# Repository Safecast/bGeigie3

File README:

## Readme

This is the Eagle CAD files for the bGeigie v2.0 (codename Delta) board.

This project is a part of the Safecast radiation monitoring project.
Find out more on [the Safecast website](http://www.safecast.org)

### License

2011 (c) Robin Scheibler
Creative Commons Attribution-ShareAlike 3.0 Unported (CC BY-SA 3.0)
For more details see (http://creativecommons.org/licenses/by-sa/3.0/)

## Design

### Main microcontroller

Atmega1284p.

### Power supply

The system is powered by a LiPo battery providing 4.2V at full charge and dies around 3.5V.

### Battery sensing

The Atmega1284p has two internal analog references: 1.1 or 2.56.

We need to sense the battery voltage between 4.2 and 3.5V.

Let's use a voltage divider with R1 = 300K and R2 = 100K.

Then Vs = R2/(R1+R2) = 1/4*Vin, giving a range of 1.05 to 0.875V roughly. We
decide to use the 1.1 reference. This gives use roughly 160 levels of
resolution.

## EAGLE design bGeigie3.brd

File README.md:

## bGeigie3

These are the Eagle CAD files for the bGeigie v3.0 (codename NX) board.

This project is a part of the Safecast radiation monitoring project.
Find out more on [the Safecast website](http://www.safecast.org)

_Note_: although the github repo is named `bGeigie2`, the content is really the **bGeigie3**.

## License

2011-2013 (c) Robin Scheibler
Creative Commons Attribution-ShareAlike 3.0 Unported (CC BY-SA 3.0)
For more details see (http://creativecommons.org/licenses/by-sa/3.0/)

## Produce a bGeigie3

### Gerber

The gerber files can be downloaded [here](https://dl.dropboxusercontent.com/u/78009186/files/bGeigie_v3.4_gerber.zip)

### BOM

The full BOM can be found [here](https://docs.google.com/spreadsheet/ccc?key=0AvXZ3hGhBSusdEQ3NjlfN2hRUnljeTNhNEF5WDNzVWc&usp=sharing).

### Software

* [Firmware](https://github.com/Safecast/SafecastBGeigie)
* [Modded arduino IDE](https://github.com/fakufaku/Arduino) [bin](https://github.com/downloads/fakufaku/Arduino/arduino-Safecast-20121019-macosx.zip)
* [Automated programming tools](https://github.com/Safecast/SCbG3-hexes)

## Tech notes

### Power supply

The system is powered by a LiPo battery providing 4.2V at full charge and dies around 3.5V.

### Battery sensing

The Atmega1284p has two internal analog references: 1.1 or 2.56.

We need to sense the battery voltage between 4.2 and 3.5V.

Let's use a voltage divider with R1 = 100K and R2 = 120K.

Then `Vs = R2/(R1+R2) = 0.54*Vin`, giving a range of 2.3V to 1.89V roughly. We
decide to use the 2.5 reference. This gives use roughly 170 levels of
resolution.

### 50 Ohm trace for the Radio and GPS antennas

* Wiki entry on [microstrips](http://en.wikipedia.org/wiki/Microstrip)
* Microstrip impedance [calculator](http://www.cepd.com/calculators/microstrip.htm)

As a starting point, I used the following values based on [PCB Fusion](http://www.seeedstudio.com/depot/fusion-pcb-service-p-835.html?cPath=185).

* Trace width: 2.815mm (need to look-up tolerance of printing service)
* Substrate height: 1.6mm (standard from PCB Fusion)
* Copper thickness: 0.035mm (guessed from PCB Fusion characteristics, inner layer ?)

give an impedance Z=50.04 Ohms.

### Possible printing services

* [PCB Fusion](http://www.seeedstudio.com/depot/fusion-pcb-service-p-835.html?cPath=185)
* [PCB Cart](http://www.pcbcart.com/) (seems to offer manufacturing too)
* [PCB Express](http://www.pcbexpress.com/)

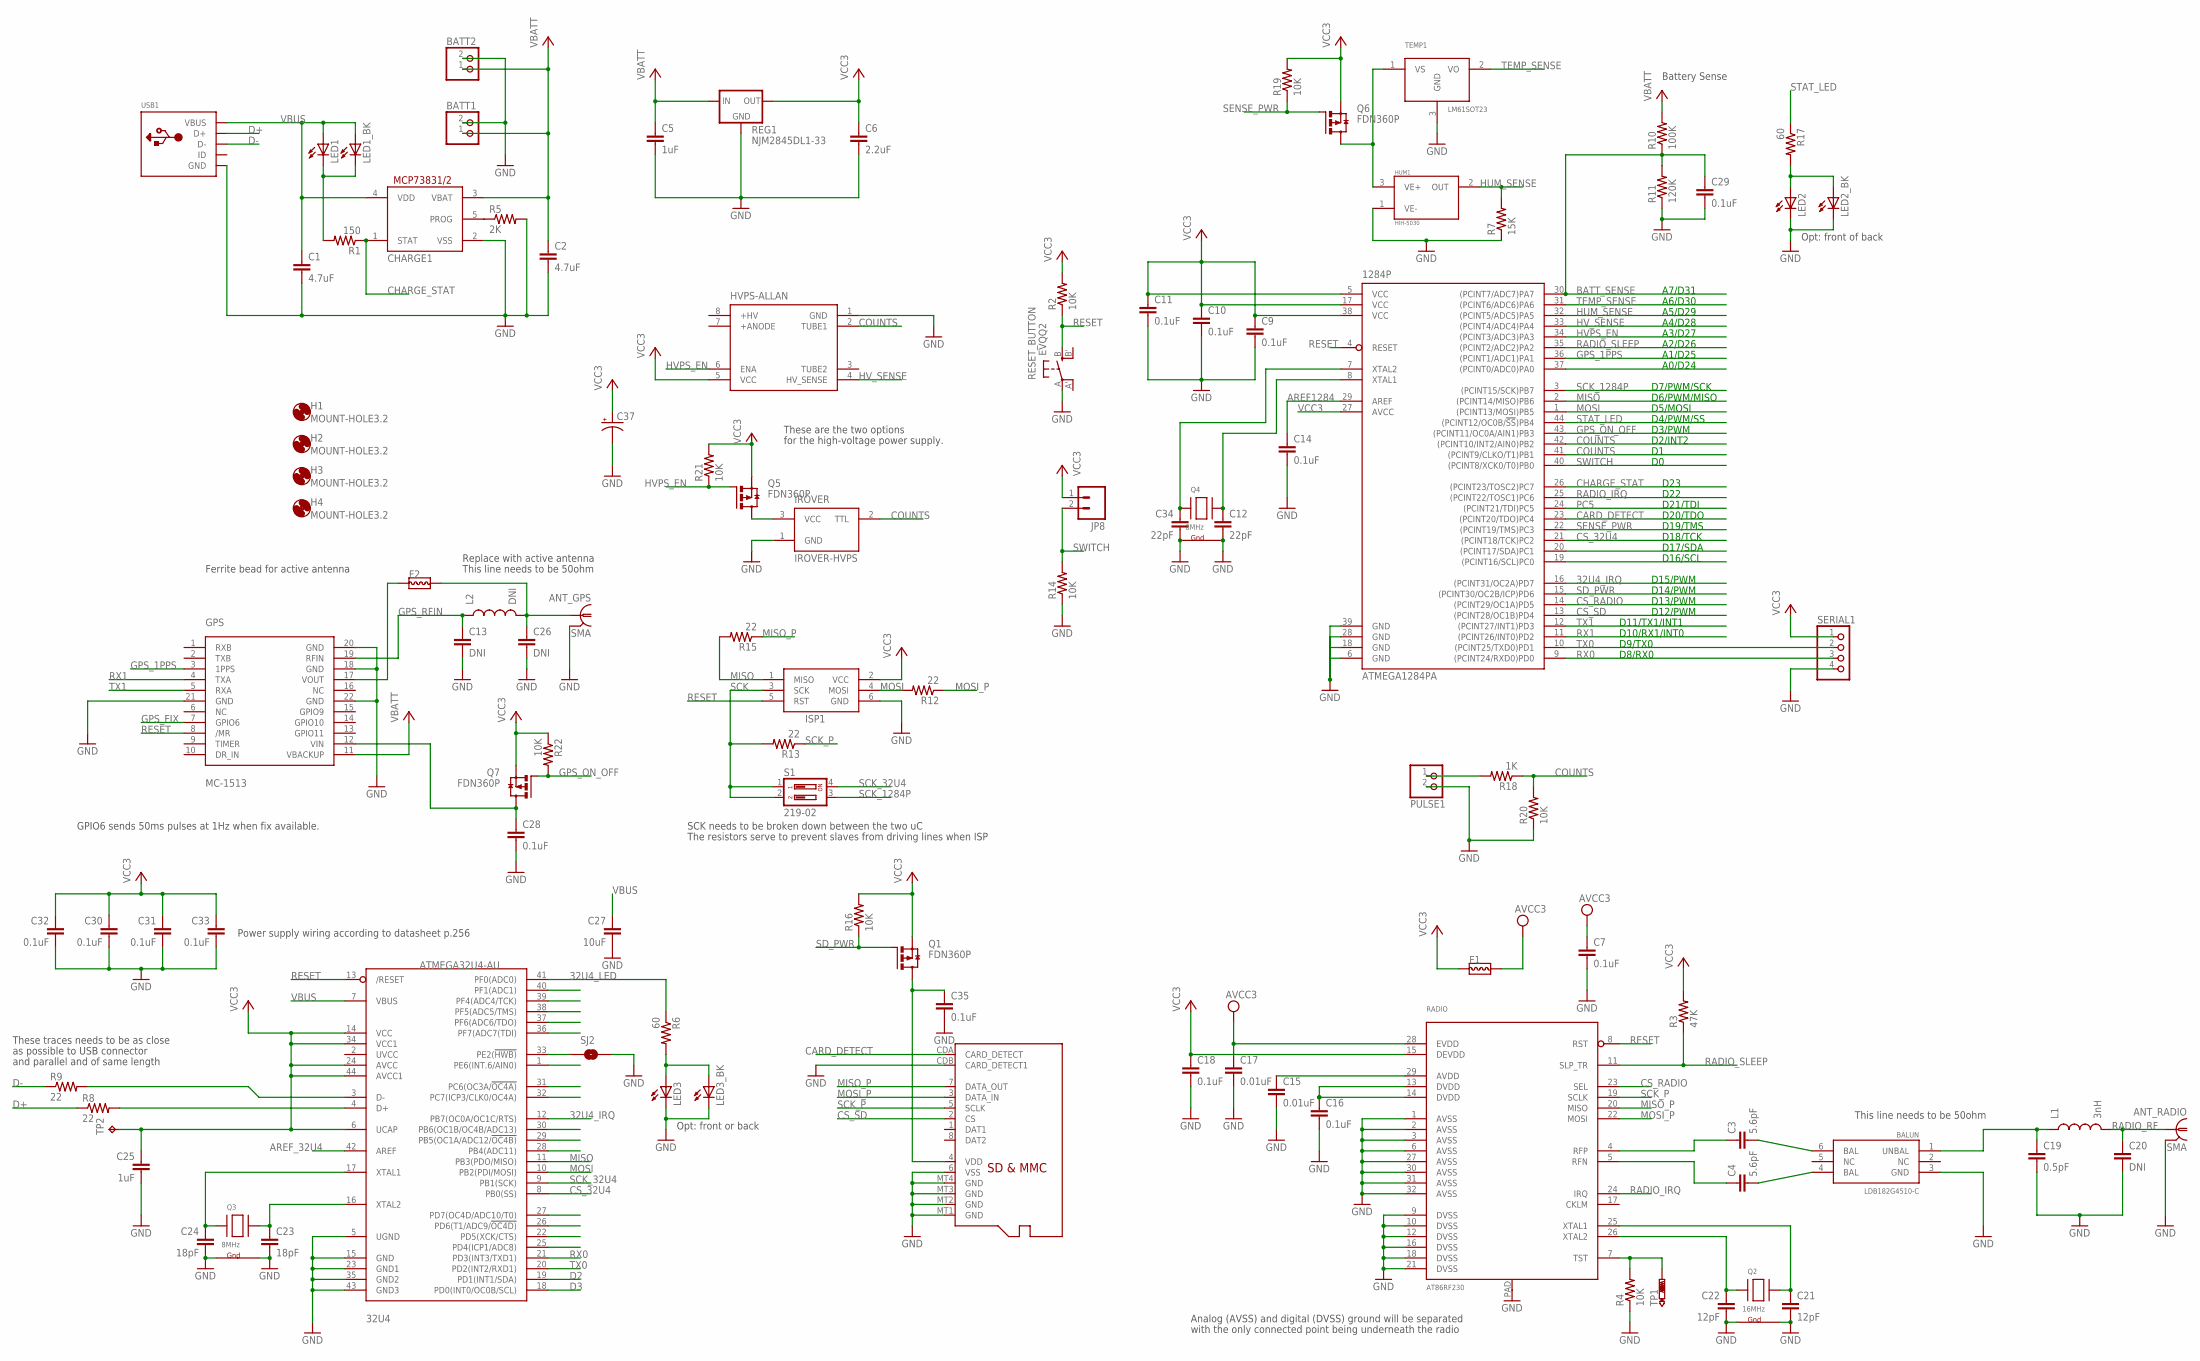
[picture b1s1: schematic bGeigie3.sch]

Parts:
32U4: ATMEGA32U4-AU; TQFP44
1284P: ATMEGA1284PA; TQFP44
ANT_GPS: SMA; LTI-SASF54GT
ANT_RADIO: SMA; LTI-SASF54GT
BALUN: LDB182G4510-C
BATT1, BATT2: JST_2PIN-THM; JST-PH-2-THM
C1, C2: 4.7uF; 0805
C3, C4: 5.6pF; 0402-CAP
C5: 1uF; 0805
C6: 2.2uF; 0805
C7, C9, C10, C11, C14, C16, C18, C28, C29, C30, C31, C32, C33, C35: 0.1uF; 0603-CAP
C12, C34: 22pF; 0603-CAP
C13, C20, C26: DNI; 0402-CAP
C15, C17: 0.01uF; 0603-CAP
C19: 0.5pF; 0402-CAP
C21, C22: 12pF; 0603-CAP
C23, C24: 18pF; 0603-CAP
C25: 1uF; 0603-CAP
C27: 10uF; 0805
C37: CPOL-USD/7343-31W; D/7343-31W
CHARGE1: MCP73831/OT; SOT23-5L
F1, F2: L-FERRITE-BEAD-0805; 0805
GPS: MC-1513; S4-1513
H1, H2, H3, H4: MOUNT-HOLE3.2; 3,2
HUM1: HIH-5030
HVPS-ALLAN: HVPS-ALLANV2-REVERSE; HVPS-ALLAN-V2-REVERSE
IROVER: IROVER-HVPS; IROVER
ISP1: AVRISP-6; AVRISP
JP8: M023.5MM; SCREWTERMINAL-3.5MM-2
L1: 3nH; C0402
L2: DNI; C0402
LED1, LED1_BK, LED2, LED2_BK, LED3, LED3_BK: LEDCHIPLED_0603; CHIPLED_0603
PULSE1: JST_2PIN-THM; JST-PH-2-THM
Q1, Q5, Q6, Q7: FDN360P; SUPER-SOT3
Q2: 16MHz; NX3225
Q3, Q4: 8MHz; CRYSTAL-5032
R1: 150; R0805
R2, R4, R14, R16, R19, R20, R21, R22: 10K; R0603
R3: 47K; R0603
R5: 2K; R0603
R6, R17: 60; R0805
R7: 15K; R0603
R8, R9, R12, R13, R15: 22; R0603
R10: 100K; R0603
R11: 120K; R0603
R18: 1K; R0603
RADIO: AT86RF230; 32QN1
REG1: NJM2845DL1-33; DPACK
RESET_BUTTON: EVQQ2; EVQ-Q2
S1: 219-02; CTS-219-02
SD: MICROSD; DM3AT-SF-PEJM5
SERIAL1: PINHD-1X4; 1X04
SJ2: SOLDERJUMPERTRACE; SJ_2S-TRACE
TEMP1: LM61SOT23; SOT23
TP1: PTR1B1,27; B1,27
TP2: TPTP15SQ; TP15SQ
USB1: USBMINIB; USB-MINIB

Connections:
32U4_IRQ: 32U4.12 (PB7(OC0A/OC1C/RTS)), 1284P.16 ((PCINT31/OC2A)PD7)
32U4_LED: 32U4.41 (PF0(ADC0)), R6.1
32U4_PC7: 32U4.32 (PC7(ICP3/CLK0/OC4A))
AREF1284: 1284P.29 (AREF), C14.1
AREF_32U4: 32U4.42 (AREF)
AVCC3: C7.1, C17.1, F1.2, RADIO.28 (EVDD)
BATT_SENSE: 1284P.30 ((PCINT7/ADC7)PA7), C29.1, R10.1, R11.2
CARD_DETECT: 1284P.23 ((PCINT20/TDO)PC4), SD.CDA (CARD_DETECT)
CHARGE_STAT: 1284P.26 ((PCINT23/TOSC2)PC7), CHARGE1.1 (STAT), R1.1
COUNTS: 1284P.41 ((PCINT9/CLKO/T1)PB1), 1284P.42 ((PCINT10/INT2/AIN0)PB2), HVPS-ALLAN.2 (TUBE1), IROVER.2 (TTL), R18.1, R20.2
CS_32U4: 32U4.8 (PB0(SS)), 1284P.21 ((PCINT18/TCK)PC2)
CS_RADIO: 1284P.14 ((PCINT29/OC1A)PD5), RADIO.23 (SEL)
CS_SD: 1284P.13 ((PCINT28/OC1B)PD4), SD.2 (CS)
D2: 32U4.19 (PD1(INT1/SDA))
D3: 32U4.18 (PD0(INT0/OC0B/SCL))
D+: R8.1, USB1.D+
D-: R9.1, USB1.D-
GND: 32U4.5 (UGND), 32U4.15 (GND), 32U4.23 (GND1), 32U4.35 (GND2), 32U4.43 (GND3), 1284P.6 (GND), 1284P.18 (GND), 1284P.28 (GND), 1284P.39 (GND), ANT_GPS.2 (GND), ANT_GPS.3 (GND), ANT_GPS.4 (GND), ANT_GPS.5 (GND), ANT_RADIO.2 (GND), ANT_RADIO.3 (GND), ANT_RADIO.4 (GND), ANT_RADIO.5 (GND), BALUN.3 (GND), BATT1.2 (1), BATT2.2 (1), C1.2, C2.2, C5.2, C6.2, C7.2, C9.2, C10.2, C11.2, C12.2, C13.2, C14.2, C15.2, C16.2, C17.2, C18.2, C19.2, C20.2, C21.2, C22.2, C23.2, C24.2, C25.2, C26.2, C27.2, C28.2, C29.2, C30.2, C31.2, C32.2, C33.2, C34.2, C35.2, C37.-, CHARGE1.2 (VSS), GPS.18 (GND), GPS.20 (GND), GPS.21 (GND), GPS.22 (GND), HUM1.1 (VE-), HVPS-ALLAN.1 (GND), IROVER.1 (GND), ISP1.6 (GND), LED2.C, LED2_BK.C, LED3.C, LED3_BK.C, PULSE1.2 (1), Q2.2 (G2), Q2.4 (G1), Q3.2 (G1), Q3.4 (G2), Q4.2 (G1), Q4.4 (G2), R4.1, R5.2, R7.1, R11.1, R14.1, R20.1, RADIO.1 (AVSS), RADIO.2 (AVSS), RADIO.3 (AVSS), RADIO.6 (AVSS), RADIO.9 (DVSS), RADIO.10 (DVSS), RADIO.12 (DVSS), RADIO.16 (DVSS), RADIO.18 (DVSS), RADIO.21 (DVSS), RADIO.27 (AVSS), RADIO.30 (AVSS), RADIO.31 (AVSS), RADIO.32 (AVSS), RADIO.PAD, REG1.4 (GND), RESET_BUTTON.A, SD.6 (VSS), SD.CDB (CARD_DETECT1), SD.MT1 (GND), SD.MT2 (GND), SD.MT3 (GND), SD.MT4 (GND), SERIAL1.4, SJ2.2, TEMP1.3 (GND), USB1.GND
GPS_1PPS: 1284P.36 ((PCINT1/ADC1)PA1), GPS.3 (1PPS)
GPS_FIX: GPS.7 (GPIO6)
GPS_ON_OFF: 1284P.43 ((PCINT11/OC0A/AIN1)PB3), Q7.1 (G), R22.2
GPS_RFIN: C13.1, GPS.19 (RFIN), L2.1
HUM_SENSE: 1284P.32 ((PCINT5/ADC5)PA5), HUM1.2 (OUT), R7.2
HVPS_EN: 1284P.34 ((PCINT3/ADC3)PA3), HVPS-ALLAN.6 (ENA), Q5.1 (G), R21.1
HV_SENSE: 1284P.33 ((PCINT4/ADC4)PA4), HVPS-ALLAN.4 (HV_SENSE)
MISO: 32U4.11 (PB3(PDO/MISO)), 1284P.2 ((PCINT14/MISO)PB6), ISP1.1 (MISO), R15.2
MISO_P: R15.1, RADIO.20 (MISO), SD.7 (DATA_OUT)
MOSI: 32U4.10 (PB2(PDI/MOSI)), 1284P.1 ((PCINT13/MOSI)PB5), ISP1.4 (MOSI), R12.2
MOSI_P: R12.1, RADIO.22 (MOSI), SD.3 (DATA_IN)
unnamed: 32U4.16 (XTAL2), C23.1, Q3.3 (X2)
unnamed: LED1.C, LED1_BK.C, R1.2
unnamed: PULSE1.1 (2), R18.2
unnamed: CHARGE1.5 (PROG), R5.1
unnamed: BALUN.4 (BAL), C4.2
unnamed: 1284P.8 (XTAL1), C12.1, Q4.3 (X2)
unnamed: 1284P.7 (XTAL2), C34.1, Q4.1 (X1)
unnamed: C16.1, RADIO.13 (DVDD), RADIO.14 (DVDD)
unnamed: C15.1, RADIO.29 (AVDD)
unnamed: ANT_GPS.1, C26.1, F2.2, L2.2
unnamed: C21.1, Q2.3 (X2), RADIO.25 (XTAL1)
unnamed: C22.1, Q2.1 (X1), RADIO.26 (XTAL2)
unnamed: F2.1, GPS.17 (VOUT)
unnamed: IROVER.3 (VCC), Q5.3 (D)
unnamed: LED3.A, LED3_BK.A, R6.2
unnamed: R4.2, RADIO.7 (TST), TP1.TP
unnamed: BALUN.6 (BAL), C3.2
unnamed: C4.1, RADIO.5 (RFN)
unnamed: C3.1, RADIO.4 (RFP)
unnamed: BALUN.1 (UNBAL), C19.1, L1.1
unnamed: C28.1, GPS.12 (VIN), Q7.3 (D)
unnamed: 32U4.17 (XTAL1), C24.1, Q3.1 (X1)
unnamed: LED2.A, LED2_BK.A, R17.2
unnamed: 32U4.3 (D-), R9.2
unnamed: 32U4.4 (D+), R8.2
unnamed: 32U4.33 (PE2(!HWB)), SJ2.1
PA0: 1284P.37 ((PCINT0/ADC0)PA0)
PC0: 1284P.19 ((PCINT16/SCL)PC0)
PC1: 1284P.20 ((PCINT17/SDA)PC1)
PC5: 1284P.24 ((PCINT21/TDI)PC5)
RADIO_IRQ: 1284P.25 ((PCINT22/TOSC1)PC6), RADIO.24 (IRQ)
RADIO_RF: ANT_RADIO.1, C20.1, L1.2
RADIO_SLEEP: 1284P.35 ((PCINT2/ADC2)PA2), R3.1, RADIO.11 (SLP_TR)
RESET: 32U4.13 (/RESET), 1284P.4 (RESET), GPS.8 (/MR), ISP1.5 (RST), R2.1, RADIO.8 (RST), RESET_BUTTON.B (S)
RX0: 32U4.21 (PD3(INT3/TXD1)), 1284P.9 ((PCINT24/RXD0)PD0), SERIAL1.3
RX1: 1284P.11 ((PCINT26/INT0)PD2), GPS.4 (TXA)
SCK: ISP1.3 (SCK), R13.2, S1.1, S1.2
SCK_32U4: 32U4.9 (PB1(SCK)), S1.4
SCK_1284P: 1284P.3 ((PCINT15/SCK)PB7), S1.3
SCK_P: R13.1, RADIO.19 (SCLK), SD.5 (SCLK)
SD_PWR: 1284P.15 ((PCINT30/OC2B/ICP)PD6), Q1.1 (G), R16.1
SENSE: HUM1.3 (VE+), Q6.3 (D), TEMP1.1 (VS)
SENSE_PWR: 1284P.22 ((PCINT19/TMS)PC3), Q6.1 (G), R19.1
STAT_LED: 1284P.44 ((PCINT12/OC0B/!SS!)PB4), R17.1
SWITCH: 1284P.40 ((PCINT8/XCK0/T0)PB0), JP8.2, R14.2
TEMP_SENSE: 1284P.31 ((PCINT6/ADC6)PA6), TEMP1.2 (VO)
TX0: 32U4.20 (PD2(INT2/RXD1)), 1284P.10 ((PCINT25/TXD0)PD1), SERIAL1.2
TX1: 1284P.12 ((PCINT27/INT1)PD3), GPS.5 (RXA)
VBATT: BATT1.1 (2), BATT2.1 (2), C2.1, C5.1, CHARGE1.3 (VBAT), GPS.11 (VBACKUP), R10.2, REG1.1 (IN)
VBUS: 32U4.7 (VBUS), C1.1, C27.1, CHARGE1.4 (VDD), LED1.A, LED1_BK.A, USB1.VBUS
VCC3: 32U4.6 (UCAP), 32U4.14 (VCC), 32U4.24 (AVCC), 32U4.34 (VCC1), 32U4.44 (AVCC1), 1284P.5 (VCC), 1284P.17 (VCC), 1284P.27 (AVCC), 1284P.38 (VCC), C6.1, C9.1, C10.1, C11.1, C18.1, C25.1, C30.1, C31.1, C32.1, C33.1, C37.+, F1.1, HVPS-ALLAN.5 (VCC), ISP1.2 (VCC), JP8.1, Q1.2 (S), Q5.2 (S), Q6.2 (S), Q7.2 (S), R2.2, R3.2, R16.2, R19.2, R21.2, R22.1, RADIO.15 (DEVDD), REG1.3 (OUT), SERIAL1.1, TP2.TP
VDD: C35.1, Q1.3 (D), SD.4 (VDD)

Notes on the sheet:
D2/INT2
D3/PWM
D4/PWM/SS
D5/MOSI
D6/PWM/MISO
D7/PWM/SCK
D8/RX0
D9/TX0
D11/TX1/INT1
D10/RX1/INT0
D12/PWM
D13/PWM
D14/PWM
D15/PWM
D16/SCL
D17/SDA
D18/TCK
D19/TMS
D20/TDO
D21/TDI
D22
D23
A0/D24
A1/D25
A2/D26
A3/D27
A4/D28
A5/D29
A6/D30
A7/D31
Battery Sense
GPIO6 sends 50ms pulses at 1Hz when fix available.
SCK needs to be broken down between the two uC
The resistors serve to prevent slaves from driving lines when ISP
This line needs to be 50ohm
These traces needs to be as close
as possible to USB connector
and parallel and of same length
Replace with active antenna
Analog (AVSS) and digital (DVSS) ground will be separated

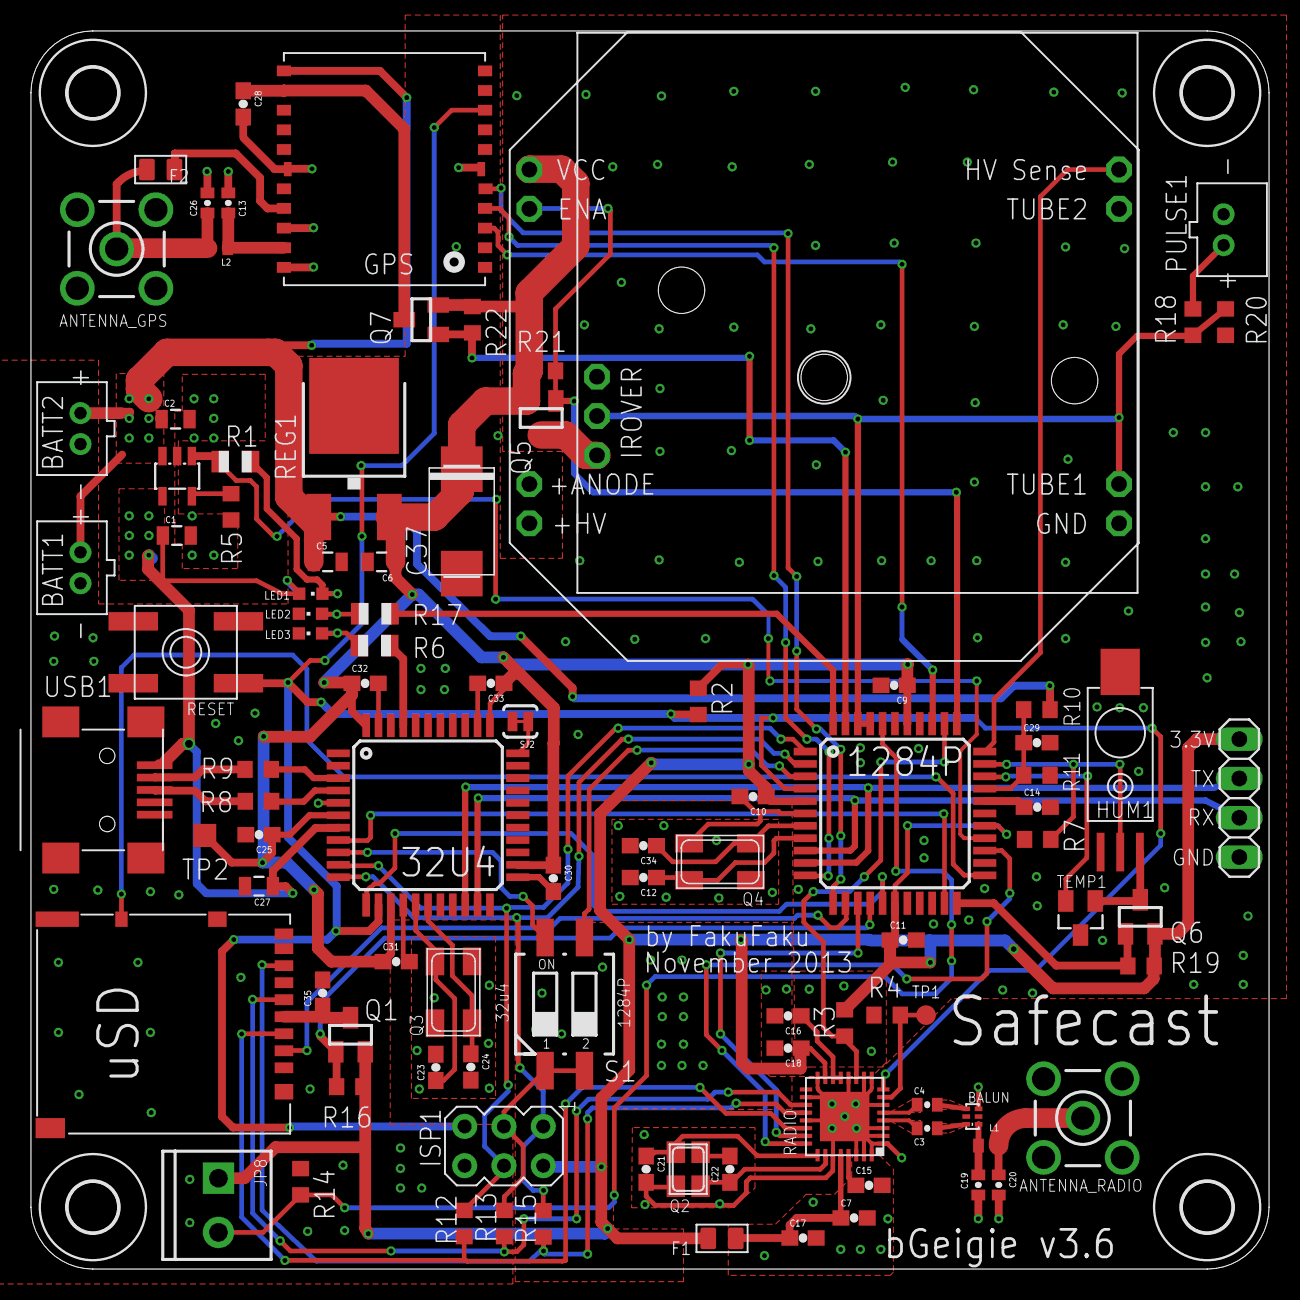
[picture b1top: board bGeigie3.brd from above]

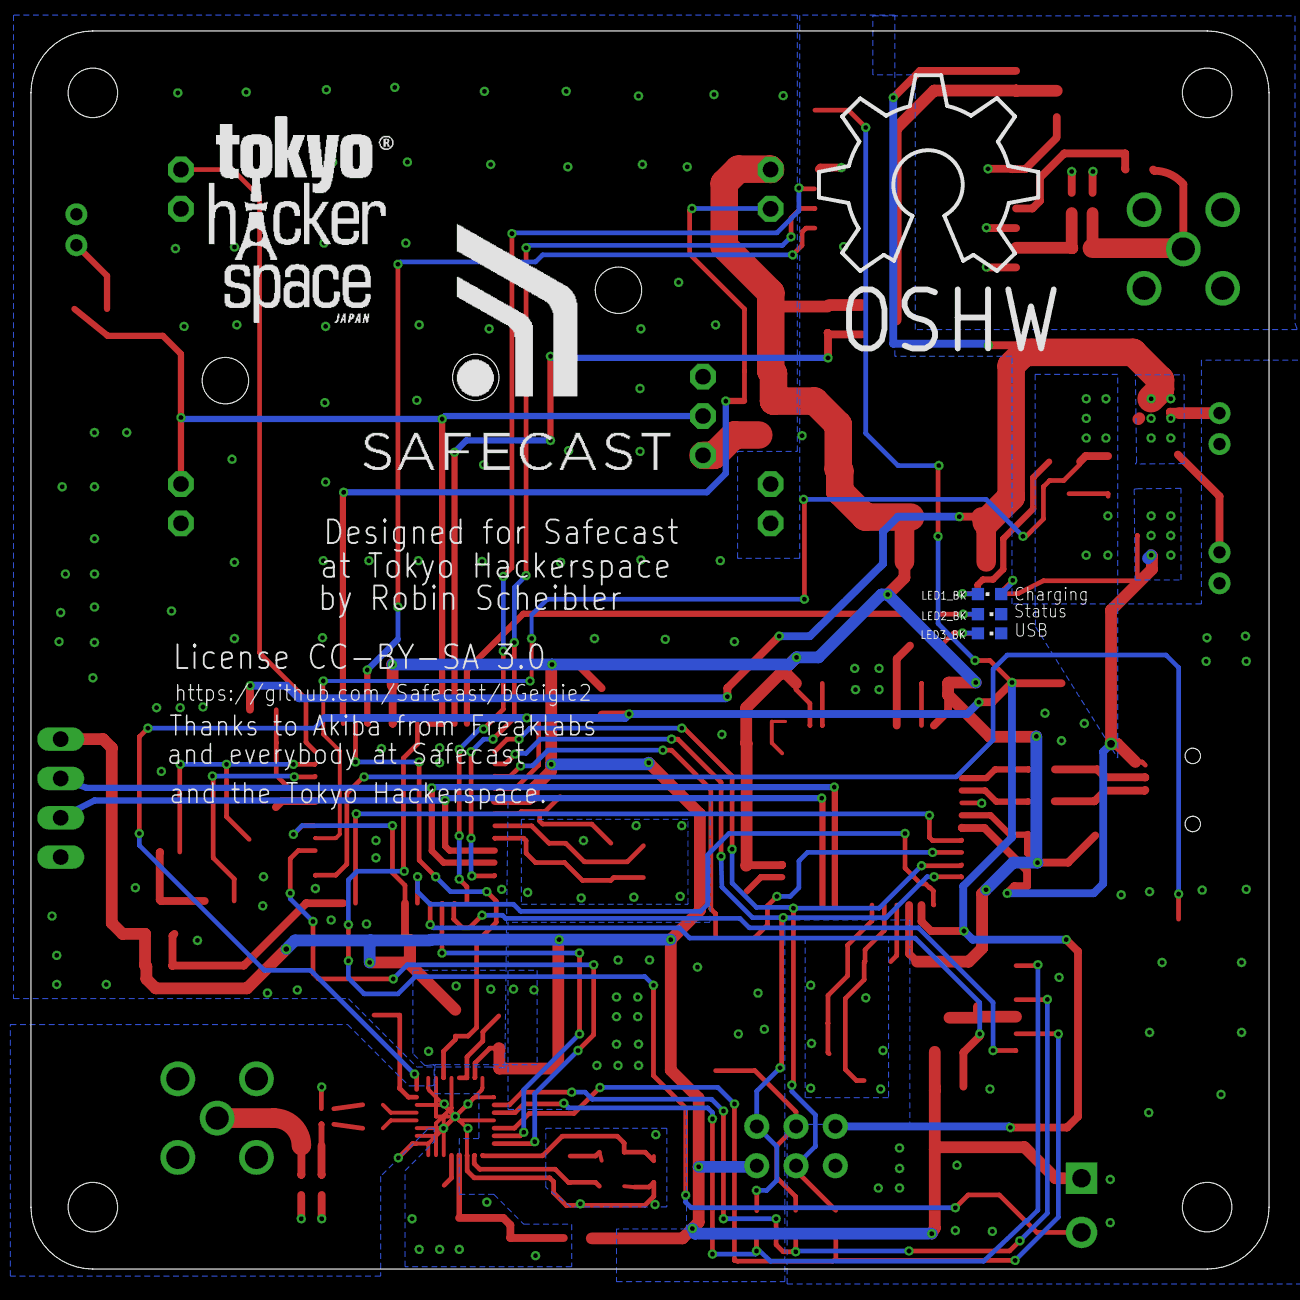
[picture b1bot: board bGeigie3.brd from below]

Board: 2 copper layers, 80.0 x 80.0 mm, 107 parts (6 on the bottom side), 72 nets.

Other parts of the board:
U$1: SAFECAST_LOGO
U$3: THS
U$4: OSHW_10X500_NOTEXT

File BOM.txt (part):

Partlist

Exported from bGeigie2.sch at 13.09.12 17:58

EAGLE Version 5.11.0 Copyright (c) 1988-2010 CadSoft

Part         Value                Device               Package               Library          Sheet

32U4         ATMEGA32U4-AU        ATMEGA32U4-AU        TQFP44                adafruit         1
1284P        ATMEGA1284PA         ATMEGA1284PA         TQFP44                Robin            1
ANT_GPS      SMA                  LTI-SASF54GT         LTI-SASF54GT          con-coax         1
ANT_RADIO    SMA                  LTI-SASF54GT         LTI-SASF54GT          con-coax         1
BALUN        LDB182G4510-C        LDB182G4510-C        LDB182G4510-C         Robin            1
BATT1                             JST_2PIN-THM         JST-PH-2-THM          adafruit         1
BATT2                             JST_2PIN-THM         JST-PH-2-THM          adafruit         1
C1           4.7uF                CAP0805              0805                  SparkFun         1
C2           4.7uF                CAP0805              0805                  SparkFun         1
C3           5.6pF                CAP0402-CAP          0402-CAP              SparkFun         1
C4           5.6pF                CAP0402-CAP          0402-CAP              SparkFun         1
C5           1uF                  CAP0805              0805                  SparkFun         1
C6           2.2uF                CAP0805              0805                  SparkFun         1
C7           0.1uF                CAP0603-CAP          0603-CAP              SparkFun         1
C8           0.1uF                CAP0603-CAP          0603-CAP              SparkFun         1
C9           0.1uF                CAP0603-CAP          0603-CAP              SparkFun         1
C10          0.1uF                CAP0603-CAP          0603-CAP              SparkFun         1
C11          0.1uF                CAP0603-CAP          0603-CAP              SparkFun         1
C12          22pF                 CAP0603-CAP          0603-CAP              SparkFun         1
C13          DNI                  CAP0402-CAP          0402-CAP              SparkFun         1
C14          0.1uF                CAP0603-CAP          0603-CAP              SparkFun         1
C15          0.01uF               CAP0603-CAP          0603-CAP              SparkFun         1
C16          0.1uF                CAP0603-CAP          0603-CAP              SparkFun         1
C17          0.01uF               CAP0603-CAP          0603-CAP              SparkFun         1
C18          0.1uF                CAP0603-CAP          0603-CAP              SparkFun         1
C19          0.5pF                CAP0402-CAP          0402-CAP              SparkFun         1
C20          DNI                  CAP0402-CAP          0402-CAP              SparkFun         1
C21          12pF                 CAP0603-CAP          0603-CAP              SparkFun         1
C22          12pF                 CAP0603-CAP          0603-CAP              SparkFun         1
C23          18pF                 CAP0603-CAP          0603-CAP              SparkFun         1
C24          18pF                 CAP0603-CAP          0603-CAP              SparkFun         1
C25          1uF                  CAP0603-CAP          0603-CAP              SparkFun         1
C26          DNI                  CAP0402-CAP          0402-CAP              SparkFun         1
C27          10uF                 CAP0805              0805                  SparkFun         1
C28          0.1uF                CAP0603-CAP          0603-CAP              SparkFun         1
C29          0.1uF                CAP0603-CAP          0603-CAP              SparkFun         1
C30          0.1uF                CAP0603-CAP          0603-CAP              SparkFun         1
C31          0.1uF                CAP0603-CAP          0603-CAP              SparkFun         1
C32          0.1uF                CAP0603-CAP          0603-CAP              SparkFun         1
C33          0.1uF                CAP0603-CAP          0603-CAP              SparkFun         1
C34          22pF                 CAP0603-CAP          0603-CAP              SparkFun         1
C35          0.1uF                CAP0603-CAP          0603-CAP              SparkFun         1
C36          0.1uF                CAP0603-CAP          0603-CAP              SparkFun         1
C37                               CPOL-USD/7343-31W    D/7343-31W            Robin            1
CHARGE1      MCP73831/OT          MCP73831/OT          SOT23-5L              adafruit         1
F1                                L-FERRITE-BEAD-0805  0805                  Discreter        1
F2                                L-FERRITE-BEAD-0805  0805                  Discreter        1
GPS          MC-1513              MC-1513              S4-1513               Robin            1
HUM1         HIH-5030             HIH-5030             HIH-5030              Robin            1
HVPS-ALLAN   HVPS-ALLANV2-REVERSE HVPS-ALLANV2-REVERSE HVPS-ALLAN-V2-REVERSE Robin            1
IROVER       IROVER-HVPS          IROVER-HVPS          IROVER                Robin            1
ISP1         AVRISP-6             AVRISP-6             AVRISP                adafruit         1
JP2                               PINHD-1X6/90         1X06/90               pinhead          1
JP3                               PINHD-1X6/90         1X06/90               pinhead          1
JP8                               M023.5MM             SCREWTERMINAL-3.5MM-2 SparkFun         1
L1           3nH                  INDUCTOR0402         C0402                 SparkFun         1
L2           DNI                  INDUCTOR0402         C0402                 SparkFun         1
LED1                              LEDCHIPLED_0603      CHIPLED_0603          adafruit         1
LED1_BK                           LEDCHIPLED_0603      CHIPLED_0603          adafruit         1
LED2                              LEDCHIPLED_0603      CHIPLED_0603          adafruit         1
LED2_BK                           LEDCHIPLED_0603      CHIPLED_0603          adafruit         1
LED3                              LEDCHIPLED_0603      CHIPLED_0603          adafruit         1
LED3_BK                           LEDCHIPLED_0603      CHIPLED_0603          adafruit         1
PULSE1                            JST_2PIN-THM         JST-PH-2-THM          adafruit         1
Q1           FDN360P              FDN360P              SUPER-SOT3            transistor-power 1
Q2           16MHz                XTAL-4-3225          NX3225                adafruit         1
Q3           8MHz                 XTAL-4               CRYSTAL-5032          Robin            1
Q4           8MHz                 XTAL-4               CRYSTAL-5032          Robin            1
Q5           FDN360P              FDN360P              SUPER-SOT3            transistor-power 1
Q6           FDN360P              FDN360P              SUPER-SOT3            transistor-power 1
Q7           FDN360P              FDN360P              SUPER-SOT3            transistor-power 1
R1           150                  R-US_R0805           R0805                 adafruit         1
R2           10K                  R-US_R0603           R0603                 adafruit         1
R3           47K                  R-US_R0603           R0603                 adafruit         1
R4           10K                  R-US_R0603           R0603                 adafruit         1
R5           2K                   R-US_R0603           R0603                 adafruit         1
R6           60                   R-US_R0805           R0805                 adafruit         1
R7           15K                  R-US_R0603           R0603                 adafruit         1
R8           22                   R-US_R0603           R0603                 adafruit         1
R9           22                   R-US_R0603           R0603                 adafruit         1
R10          100K                 R-US_R0603           R0603                 adafruit         1
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
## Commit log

2011-12-08 Added content and License to README file. Added .gitignore file and placeholder file for Bill Of Material (BOM.txt).
2011-12-08 Added junk files from Eagle CAD to .gitignore
2011-12-08 Added TODO.txt file to keep track of what's left to do.
2011-12-08 Added png schematics file
2011-12-19 Commiting current status of 'low-power' version.
2011-12-27 Added chipselects, IRQ. 1284p is now master of all devices. Optional serial connection between 32u4 and 1284p.
2012-01-06 Added boost converter. Edited TODO with current tasks. Now board is at 3.3V.
2012-01-07 Started to check all foot print, began the BOM.
2012-01-09 UPdated todo, started checking all footprints.
2012-01-12 More details. Updated TODO.
2012-01-12 Suffixed README with markdown extension.
2012-01-12 Suffixed README with .md.
2012-01-12 Updated PNG
2012-01-13 Added 'breakout 32u4 pins' to todo list.
2012-01-13 Updated README with impedance of RF line (GPS, Radio), and printing services.
2012-01-13 More changes
2012-01-13 Added board file.|
2012-01-17 Schematics nearly done. (Will need HVPS soon though). Added and started the board layout.
2012-01-17 Added layout png
2012-01-17 Updated schematics png, .gitignore.
2012-01-19 Advanced board layout a bit. Corrected few bugs in schematics.
2012-02-19 Moved GPS, laid radio, more wires laid out.
2012-02-20 Pulled some more wires. Finished GPS.
2012-02-20 Updated BOM, layout and schematics png.
2012-02-25 Mostly finished routing.
2012-02-25 Modified High Voltage board for v2.0. Updated PNGs.
2012-02-27 Corrected crystal. Cleaned labels. Added pull-down on audio jack. Added humidity sensor. Transistor on sensors supplies.
2012-02-29 Added iRover trace. Connected 32u4 to interrupt of 1284p. Updated BOM.
2012-03-01 Corrected hole sizes of iRover and Allan's HVPS board.
2012-03-05 Corrected audio jack footprint.
2012-03-05 Added Safecast and THS logo.
2012-03-06 Removed bottom LED labels.
2012-03-06 Added SMD footprint for LEDs on backside.
2012-03-07 Corrected values of R10, R11 and C5.
2012-03-07 Changed info about battery sensing in README.
2012-03-08 Changed footprint of 8MHz crystals.
2012-03-31 Rerouted MOSI to 32u4
2012-04-11 Replaced bipolar pnp transistors by p-channel mosfet.
2012-04-11 Added mosfet on GPS powerline. Modified GPS library part to conform to datasheet v1.4.
2012-04-12 Placed and routed MOSFET transistors.
2012-04-12 Added LED for 32u4 on pin 13.
2012-04-12 Moved 1284p led to arduino digital pin 13, routed 32u4 led on board.
2012-04-12 Corrected SPI bug.
2012-04-12 Updated PNGs.
2012-04-12 Make board corners rounded.
2012-04-24 Added credits, logo and art. Moved bead from gps antenna power.
2012-06-08 Reduced board size. Implemented everything learnt from prototypes. Go to version 3.3.
2012-06-08 Small connection was missing on a radio pad.
2012-06-09 Put C13, C26, and C19, C20 to different grounds. Updated layout PNG.
2012-06-09 Finalizing before fab.
2012-06-22 Corrected bug (unconnected wires). Rewired VCC so that power to 32u4 and 1284 are fairly independant, easy to split.
2012-07-07 Added big tantalum cap on power supply line to HVPS.
2012-07-27 Added dot in silkscreen of GPS footprint for orientation of chip.
2012-07-27 Renamed board png to bGeigie2_brd.png for consistency.
2012-09-13 Added top and bottom PNGs. Added mechanical design files for lazer cutting.
2012-09-13 Moved some labels. Added some silkscreen for 8MHz crystals. Added some tDocu for art on humidity sensor.
2012-10-28 Updated silkscreen with missing labels.
2013-08-01 Cleaning up. Upgrading name. Adding to README.
2013-11-02 Moved to Eagle CAD 6.5.0 and removed serial headers. Connect both serials together.
2013-11-05 Added serial header for debugging.
2014-08-29 bGeigie3 endurance test data and analysis.
2014-08-29 Updated bGeigie3 endurance test analysis.

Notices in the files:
bGeigie3.brd:
License CC-BY-SA 3.0
